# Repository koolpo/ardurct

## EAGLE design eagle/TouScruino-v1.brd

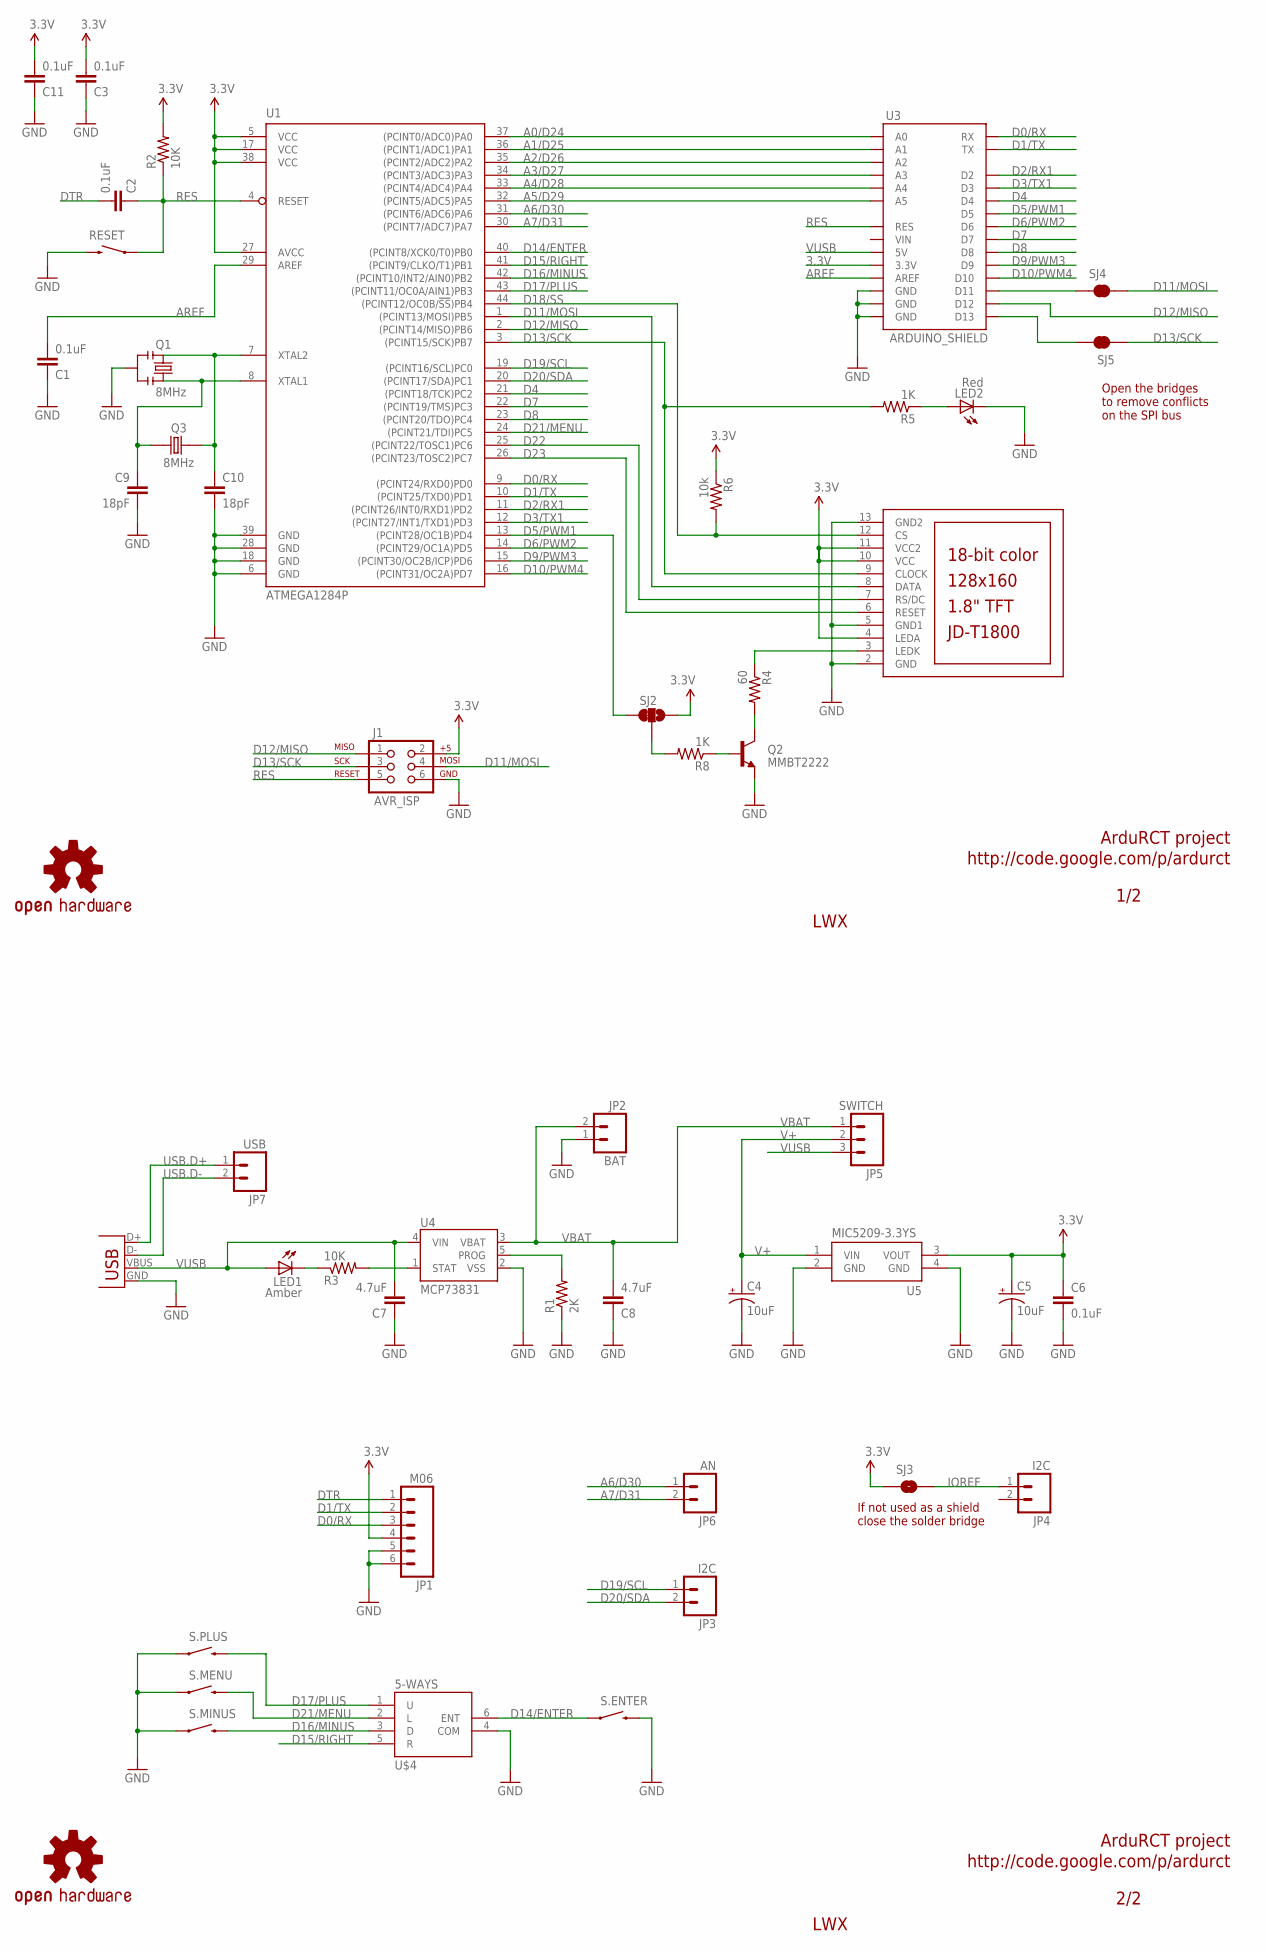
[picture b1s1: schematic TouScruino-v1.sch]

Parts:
C1, C2, C3, C6, C11: 0.1uF; 0805
C4, C5: 10uF; EIA3216
C7, C8: 4.7uF; 0805
C9, C10: 18pF; 0603-CAP
J1: AVR_ISP; 2X3
JP1: M06; 1X06
JP2: BAT; JST-2-SMD
JP3, JP4: I2C; 1X02
JP5: SWITCH; 1X3_LONGPAD
JP6: AN; 1X02
JP7: USB; 1X02
LCD1: JD-T1800
LED1: Amber; LED
LED2: Red; LED-0805
Q1: 8MHz; RESONATOR-SMD
Q2: MMBT2222; SOT23-3
Q3: 8MHz; CRYSTAL_5X3.2
R1: 2K; 0805
R2, R3: 10K; 0805
R4: 60; 0805
R5, R8: 1K; 0805
R6: 10k; 0805
RESET: SWITCH-MOMENTARY-2SMD; TACTILE_SWITCH_SMD
S.ENTER, S.MENU, S.MINUS, S.PLUS: SWITCH_SMD; TACTILE_SWITCH_SMD
SJ2: SJ_2WAYS_1-2; SJ_2WAYS_1-2_S
SJ3: SOLDERJUMPERNO; SJ_2S-NO
SJ4, SJ5: SOLDERJUMPERTRACE; SJ_2S-TRACE
U1: ATMEGA1284P; TQFP44
U3: ARDUINO_SHIELD
U4: MCP73831; SOT23-5
U5: MIC5209-3.3YS; SOT223
U$3, U$5: OSHW-LOGOM; OSHW-LOGO-M
U$4: 5-WAYS; 5-WAYS_ALPS
X1: USBSMD; USB-MINIB

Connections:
3.3V: C3.2, C5.A (+), C6.1, C11.2, J1.2, JP1.4, LCD1.4 (LEDA), LCD1.10 (VCC), LCD1.11 (VCC2), R2.2, R6.1, SJ2.3, SJ3.1, U1.5 (VCC), U1.17 (VCC), U1.27 (AVCC), U1.38 (VCC), U3.3.3V, U5.3 (VOUT)
A0/D24: U1.37 ((PCINT0/ADC0)PA0), U3.A0
A1/D25: U1.36 ((PCINT1/ADC1)PA1), U3.A1
A2/D26: U1.35 ((PCINT2/ADC2)PA2), U3.A2
A3/D27: U1.34 ((PCINT3/ADC3)PA3), U3.A3
A4/D28: U1.33 ((PCINT4/ADC4)PA4), U3.A4
A5/D29: U1.32 ((PCINT5/ADC5)PA5), U3.A5
A6/D30: JP6.1, U1.31 ((PCINT6/ADC6)PA6)
A7/D31: JP6.2, U1.30 ((PCINT7/ADC7)PA7)
AREF: C1.2, U1.29 (AREF), U3.AREF
BL_CMD: R8.2, SJ2.2
D0/RX: JP1.3, U1.9 ((PCINT24/RXD0)PD0), U3.RX
D1/TX: JP1.2, U1.10 ((PCINT25/TXD0)PD1), U3.TX
D2/RX1: U1.11 ((PCINT26/INT0/RXD1)PD2), U3.D2
D3/TX1: U1.12 ((PCINT27/INT1/TXD1)PD3), U3.D3
D4: U1.21 ((PCINT18/TCK)PC2), U3.D4
D5/PWM1: SJ2.1, U1.13 ((PCINT28/OC1B)PD4), U3.D5
D6/PWM2: U1.14 ((PCINT29/OC1A)PD5), U3.D6
D7: U1.22 ((PCINT19/TMS)PC3), U3.D7
D8: U1.23 ((PCINT20/TDO)PC4), U3.D8
D9/PWM3: U1.15 ((PCINT30/OC2B/ICP)PD6), U3.D9
D10/PWM4: U1.16 ((PCINT31/OC2A)PD7), U3.D10
D11/MOSI: J1.4, LCD1.8 (DATA), SJ4.2, U1.1 ((PCINT13/MOSI)PB5)
D12/MISO: J1.1, U1.2 ((PCINT14/MISO)PB6), U3.D12
D13/SCK: J1.3, LCD1.9 (CLOCK), R5.2, SJ5.1, U1.3 ((PCINT15/SCK)PB7)
D14/ENTER: S.ENTER.1, U1.40 ((PCINT8/XCK0/T0)PB0), U$4.6 (ENT)
D15/RIGHT: U1.41 ((PCINT9/CLKO/T1)PB1), U$4.5 (R)
D16/MINUS: S.MINUS.3 (2), U1.42 ((PCINT10/INT2/AIN0)PB2), U$4.3 (D)
D17/PLUS: S.PLUS.3 (2), U1.43 ((PCINT11/OC0A/AIN1)PB3), U$4.1 (U)
D18/SS: LCD1.12 (CS), R6.2, U1.44 ((PCINT12/OC0B/!SS!)PB4)
D19/SCL: JP3.1, U1.19 ((PCINT16/SCL)PC0)
D20/SDA: JP3.2, U1.20 ((PCINT17/SDA)PC1)
D21/MENU: S.MENU.3 (2), U1.24 ((PCINT21/TDI)PC5), U$4.2 (L)
D22: LCD1.7 (RS/DC), U1.25 ((PCINT22/TOSC1)PC6)
D23: LCD1.6 (RESET), U1.26 ((PCINT23/TOSC2)PC7)
DTR: C2.2, JP1.1
GND: C1.1, C3.1, C4.C (-), C5.C (-), C6.2, C7.1, C8.1, C9.2, C10.2, C11.1, J1.6, JP1.5, JP1.6, JP2.1, LCD1.2 (GND), LCD1.5 (GND1), LCD1.13 (GND2), LED2.2 (C), Q1.2, Q2.2 (E), R1.1, RESET.3 (2), S.ENTER.3 (2), S.MENU.1, S.MINUS.1, S.PLUS.1, U1.6 (GND), U1.18 (GND), U1.28 (GND), U1.39 (GND), U3.GND@0 (GND), U3.GND@1 (GND), U3.GND@2 (GND), U4.2 (VSS), U5.2 (GND), U5.4 (GND), U$4.4 (COM), X1.GND
IOREF: JP4.1, SJ3.2
unnamed: C9.1, Q1.1, Q3.2, U1.8 (XTAL1)
unnamed: C10.1, Q1.3, Q3.1, U1.7 (XTAL2)
unnamed: LCD1.3 (LEDK), R4.1
unnamed: Q2.1 (B), R8.1
unnamed: LED2.1 (A), R5.1
unnamed: SJ4.1, U3.D11
unnamed: LED1.C1 (C), R3.1
unnamed: SJ5.2, U3.D13
unnamed: R3.2, U4.1 (STAT)
unnamed: R1.2, U4.5 (PROG)
unnamed: Q2.3 (C), R4.2
RES: C2.1, J1.5, R2.1, RESET.1, U1.4 (RESET), U3.RES
USB.D+: JP7.1, X1.D+
USB.D-: JP7.2, X1.D-
V+: C4.A (+), JP5.2, U5.1 (VIN)
VBAT: C8.2, JP2.2, JP5.1, U4.3 (VBAT)
VUSB: C7.2, JP5.3, LED1.A1 (A), U3.5V, U4.4 (VIN), X1.VBUS

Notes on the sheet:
LWX
1/2
2/2
If not used as a shield close the solder bridge
ArduRCT project
http://code.google.com/p/ardurct
Open the bridges to remove conflicts on the SPI bus

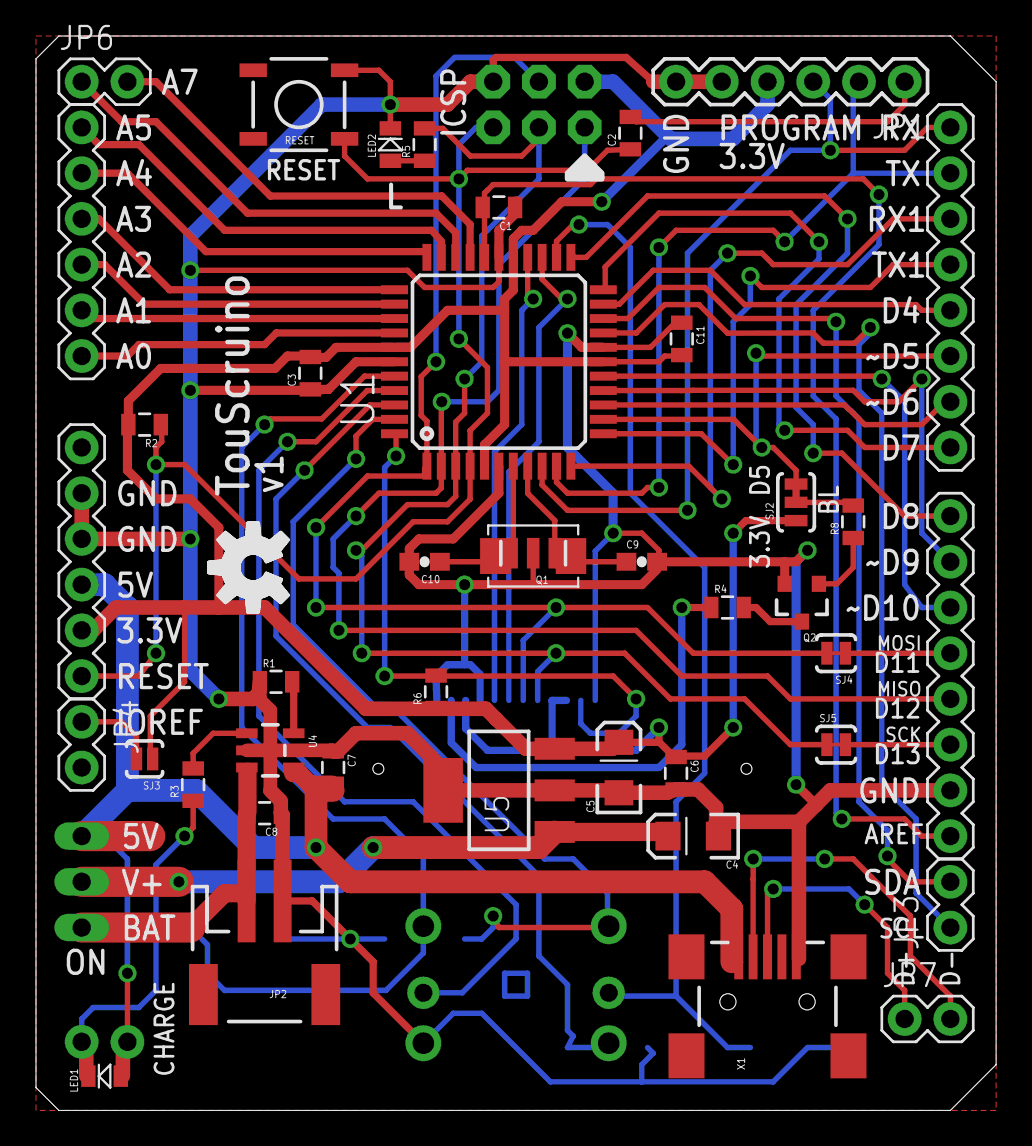
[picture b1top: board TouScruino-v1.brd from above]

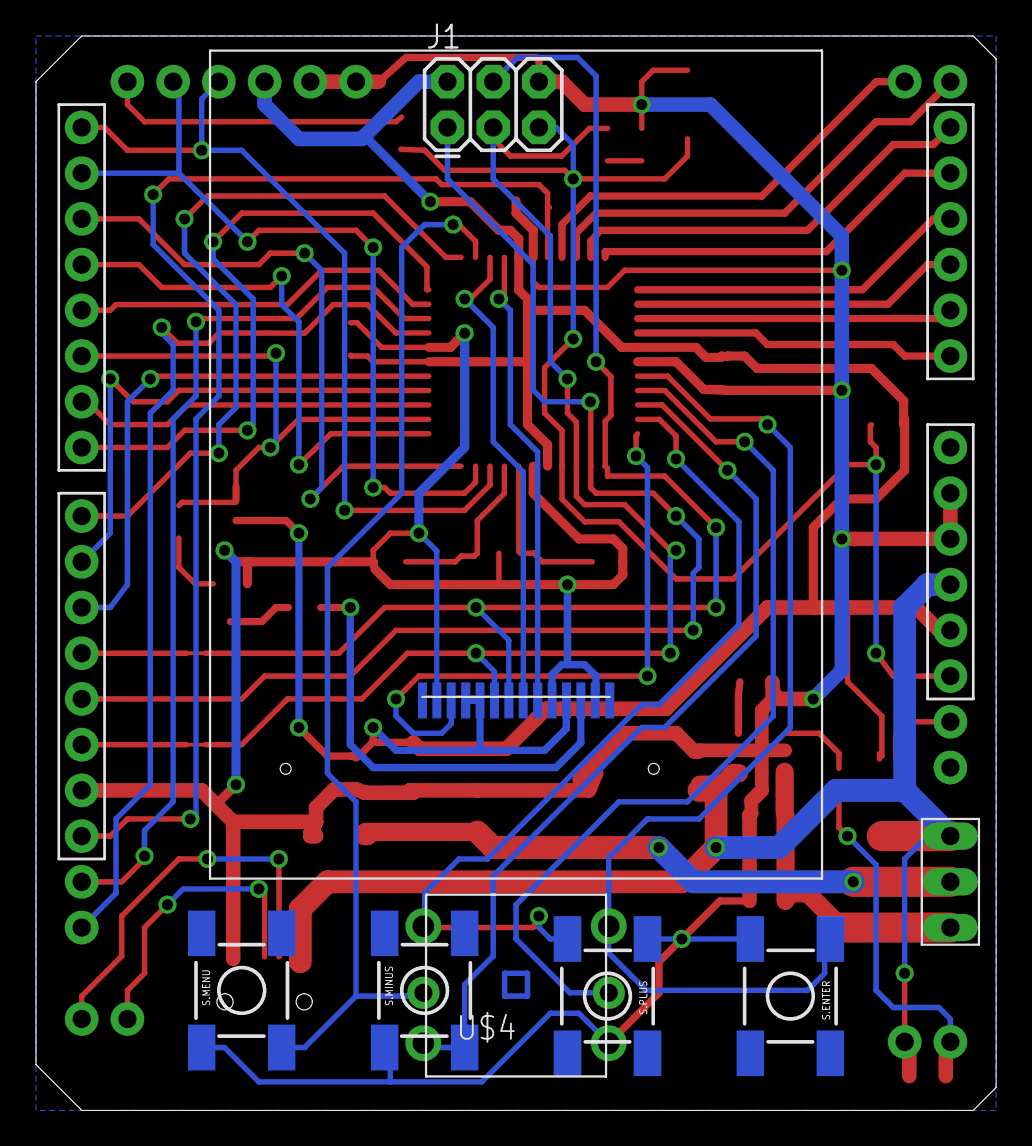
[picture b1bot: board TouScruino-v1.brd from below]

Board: 2 copper layers, 53.3 x 59.7 mm, 49 parts (9 on the bottom side), 55 nets.

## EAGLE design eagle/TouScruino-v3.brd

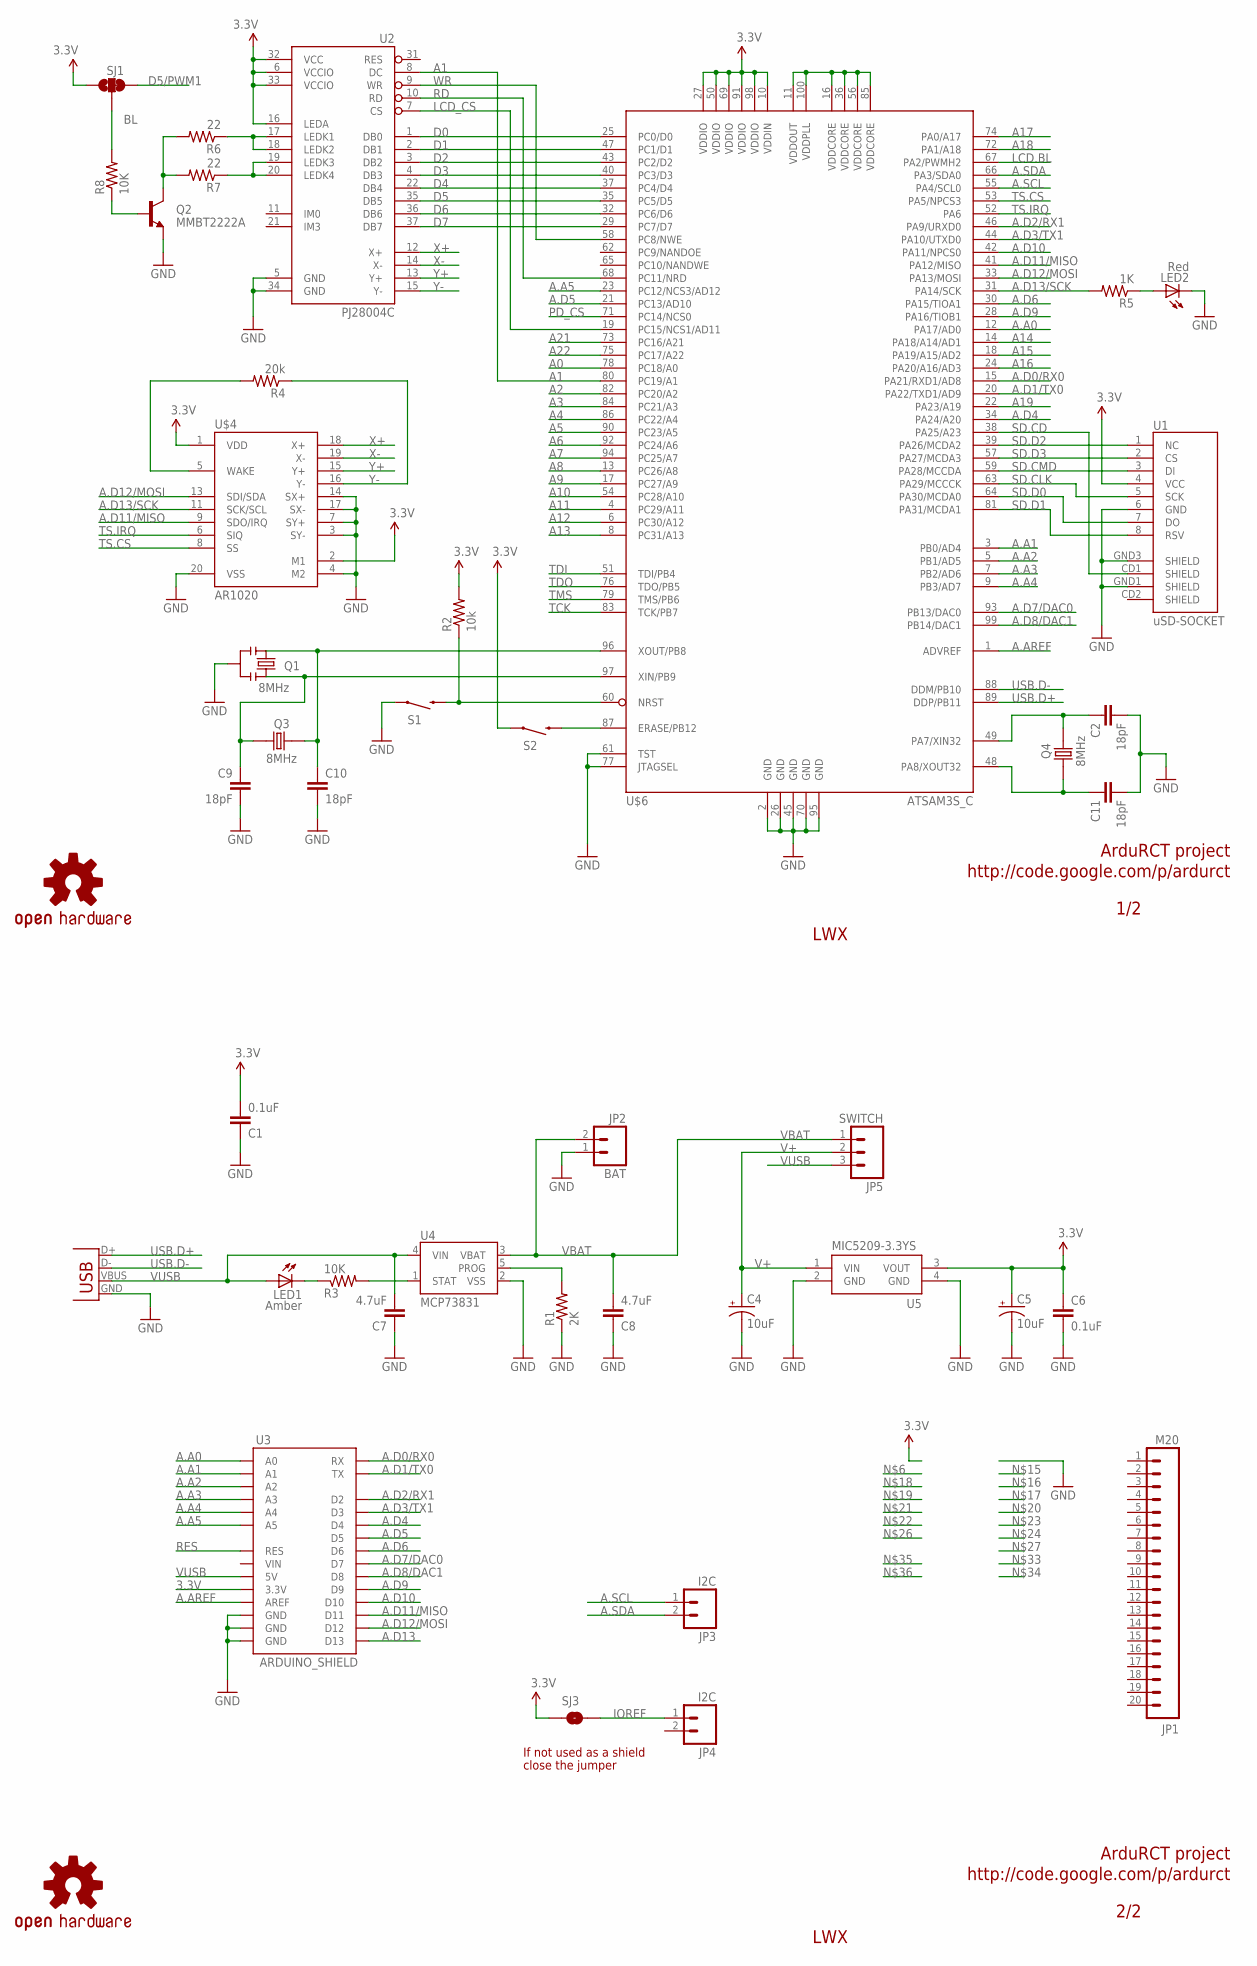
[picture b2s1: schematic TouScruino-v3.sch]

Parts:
C1, C6: 0.1uF; 0805
C2, C9, C10, C11: 18pF; 0603-CAP
C4, C5: 10uF; EIA3216
C7, C8: 4.7uF; 0805
JP1: M20; 1X20
JP2: BAT; JST-2-SMD
JP3, JP4: I2C; 1X02
JP5: SWITCH; 1X3_LONGPAD
LED1: Amber; LED
LED2: Red; LED-0805
Q1: 8MHz; RESONATOR-SMD
Q2: MMBT2222A; SOT23-3
Q3, Q4: 8MHz; CRYSTAL_5X3.2
R1: 2K; 0805
R2: 10k; 0805
R3, R8: 10K; 0805
R4: 20k; 0805
R5: 1K; 0805
R6, R7: 22; 0805
S1, S2: SWITCH-MOMENTARY-2SMD; TACTILE_SWITCH_SMD
SJ1: SJ_2WAYS_1-2; SJ_2WAYS_1-2_S
SJ3: SOLDERJUMPERNO; SJ_2S-NO
U1: uSD-SOCKET; MICRO-SD-SOCKET-PP
U2: PJ28004C
U3: ARDUINO_SHIELD
U4: MCP73831; SOT23-5
U5: MIC5209-3.3YS; SOT223
U$3, U$5: OSHW-LOGOM; OSHW-LOGO-M
U$4: AR1020; SSOP20
U$6: ATSAM3S_C; TQFP100
X1: USBSMD; USB-MINIB

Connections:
3.3V: C1.2, C5.A (+), C6.1, R2.2, S2.1, SJ1.3, SJ3.1, U1.4 (VCC), U2.6 (VCCIO), U2.16 (LEDA), U2.32 (VCC), U2.33 (VCCIO), U3.3.3V, U5.3 (VOUT), U$4.1 (VDD), U$4.2 (M1), U$6.10 (VDDIN), U$6.27 (VDDIO), U$6.50 (VDDIO), U$6.69 (VDDIO), U$6.91 (VDDIO), U$6.98 (VDDIO)
A0: U$6.78 (PC18/A0)
A1: U2.8 (DC), U$6.80 (PC19/A1)
A2: U$6.82 (PC20/A2)
A3: U$6.84 (PC21/A3)
A4: U$6.86 (PC22/A4)
A5: U$6.90 (PC23/A5)
A6: U$6.92 (PC24/A6)
A7: U$6.94 (PC25/A7)
A8: U$6.13 (PC26/A8)
A9: U$6.17 (PC27/A9)
A10: U$6.54 (PC28/A10)
A11: U$6.4 (PC29/A11)
A12: U$6.6 (PC30/A12)
A13: U$6.8 (PC31/A13)
A14: U$6.14 (PA18/A14/AD1)
A15: U$6.18 (PA19/A15/AD2)
A16: U$6.24 (PA20/A16/AD3)
A17: U$6.74 (PA0/A17)
A18: U$6.72 (PA1/A18)
A19: U$6.22 (PA23/A19)
A21: U$6.73 (PC16/A21)
A22: U$6.75 (PC17/A22)
A.A0: U3.A0, U$6.12 (PA17/AD0)
A.A1: U3.A1, U$6.3 (PB0/AD4)
A.A2: U3.A2, U$6.5 (PB1/AD5)
A.A3: U3.A3, U$6.7 (PB2/AD6)
A.A4: U3.A4, U$6.9 (PB3/AD7)
A.A5: U3.A5, U$6.23 (PC12/NCS3/AD12)
A.AREF: U3.AREF, U$6.1 (ADVREF)
A.D0/RX0: U3.RX, U$6.15 (PA21/RXD1/AD8)
A.D1/TX0: U3.TX, U$6.20 (PA22/TXD1/AD9)
A.D2/RX1: U3.D2, U$6.46 (PA9/URXD0)
A.D3/TX1: U3.D3, U$6.44 (PA10/UTXD0)
A.D4: U3.D4, U$6.34 (PA24/A20)
A.D5: U3.D5, U$6.21 (PC13/AD10)
A.D6: U3.D6, U$6.30 (PA15/TIOA1)
A.D7/DAC0: U3.D7, U$6.93 (PB13/DAC0)
A.D8/DAC1: U3.D8, U$6.99 (PB14/DAC1)
A.D9: U3.D9, U$6.28 (PA16/TIOB1)
A.D10: U3.D10, U$6.42 (PA11/NPCS0)
A.D11/MISO: U3.D11, U$4.9 (SDO/IRQ), U$6.41 (PA12/MISO)
A.D12/MOSI: U3.D12, U$4.13 (SDI/SDA), U$6.33 (PA13/MOSI)
A.D13: U3.D13
A.D13/SCK: R5.2, U$4.11 (SCK/SCL), U$6.31 (PA14/SCK)
A.SCL: JP3.1, U$6.55 (PA4/SCL0)
A.SDA: JP3.2, U$6.66 (PA3/SDA0)
BL: R8.2, SJ1.2
D0: U2.1 (DB0), U$6.25 (PC0/D0)
D1: U2.2 (DB1), U$6.47 (PC1/D1)
D2: U2.3 (DB2), U$6.43 (PC2/D2)
D3: U2.4 (DB3), U$6.40 (PC3/D3)
D4: U2.22 (DB4), U$6.37 (PC4/D4)
D5: U2.35 (DB5), U$6.35 (PC5/D5)
D5/PWM1: SJ1.1
D6: U2.36 (DB6), U$6.32 (PC6/D6)
D7: U2.37 (DB7), U$6.29 (PC7/D7)
GND: C1.1, C2.2, C4.C (-), C5.C (-), C6.2, C7.1, C8.1, C9.2, C10.2, C11.2, JP2.1, LED2.2 (C), Q1.2, Q2.2 (E), R1.1, S1.1, U1.6 (GND), U1.GND1 (SHIELD), U1.GND3 (SHIELD), U2.5 (GND), U2.34 (GND), U3.GND@0 (GND), U3.GND@1 (GND), U3.GND@2 (GND), U4.2 (VSS), U5.2 (GND), U5.4 (GND), U$4.3 (SY-), U$4.4 (M2), U$4.7 (SY+), U$4.14 (SX+), U$4.17 (SX-), U$4.20 (VSS), U$6.2 (GND), U$6.26 (GND), U$6.45 (GND), U$6.61 (TST), U$6.70 (GND), U$6.77 (JTAGSEL), U$6.95 (GND), X1.GND
IOREF: JP4.1, SJ3.2
LCD.BL: U$6.67 (PA2/PWMH2)
LCD_CS: U2.7 (CS), U$6.19 (PC15/NCS1/AD11)
unnamed: C9.1, Q1.1, Q3.2, U$6.97 (XIN/PB9)
unnamed: C10.1, Q1.3, Q3.1, U$6.96 (XOUT/PB8)
unnamed: Q2.1 (B), R8.1
unnamed: LED2.1 (A), R5.1
unnamed: Q2.3 (C), R6.2, R7.2
unnamed: LED1.C1 (C), R3.1
unnamed: R2.1, S1.3 (2), U$6.60 (NRST)
unnamed: U$6.11 (VDDOUT), U$6.16 (VDDCORE), U$6.36 (VDDCORE), U$6.56 (VDDCORE), U$6.85 (VDDCORE), U$6.100 (VDDPLL)
unnamed: R4.2, U$4.5 (WAKE)
unnamed: R3.2, U4.1 (STAT)
unnamed: R1.2, U4.5 (PROG)
unnamed: S2.3 (2), U$6.87 (ERASE/PB12)
unnamed: R7.1, U2.19 (LEDK3), U2.20 (LEDK4)
unnamed: R6.1, U2.17 (LEDK1), U2.18 (LEDK2)
unnamed: C2.1, Q4.1, U$6.49 (PA7/XIN32)
unnamed: C11.1, Q4.2, U$6.48 (PA8/XOUT32)
PD_CS: U$6.71 (PC14/NCS0)
RD: U2.10 (RD), U$6.68 (PC11/NRD)
RES: U3.RES
SD.CD: U1.CD1 (SHIELD), U$6.38 (PA25/A23)
SD.CLK: U1.5 (SCK), U$6.63 (PA29/MCCCK)
SD.CMD: U1.3 (DI), U$6.59 (PA28/MCCDA)
SD.D0: U1.7 (DO), U$6.64 (PA30/MCDA0)
SD.D1: U1.8 (RSV), U$6.81 (PA31/MCDA1)
SD.D2: U1.1 (NC), U$6.39 (PA26/MCDA2)
SD.D3: U1.2 (CS), U$6.57 (PA27/MCDA3)
TCK: U$6.83 (TCK/PB7)
TDI: U$6.51 (TDI/PB4)
TDO: U$6.76 (TDO/PB5)
TMS: U$6.79 (TMS/PB6)
TS.CS: U$4.8 (SS), U$6.53 (PA5/NPCS3)
TS.IRQ: U$4.6 (SIQ), U$6.52 (PA6)
USB.D+: U$6.89 (DDP/PB11), X1.D+
USB.D-: U$6.88 (DDM/PB10), X1.D-
V+: C4.A (+), JP5.2, U5.1 (VIN)
VBAT: C8.2, JP2.2, JP5.1, U4.3 (VBAT)
VUSB: C7.2, JP5.3, LED1.A1 (A), U3.5V, U4.4 (VIN), X1.VBUS
WR: U2.9 (WR), U$6.58 (PC8/NWE)
X+: U2.12 (X+), U$4.18 (X+)
X-: U2.14 (X-), U$4.19 (X-)
Y+: U2.13 (Y+), U$4.15 (Y+)
Y-: R4.1, U2.15 (Y-), U$4.16 (Y-)

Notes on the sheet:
LWX
1/2
2/2
If not used as a shield
close the jumper
ArduRCT project
http://code.google.com/p/ardurct

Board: 2 copper layers, 43 parts (3 on the bottom side), 73 nets, no tracks yet.
